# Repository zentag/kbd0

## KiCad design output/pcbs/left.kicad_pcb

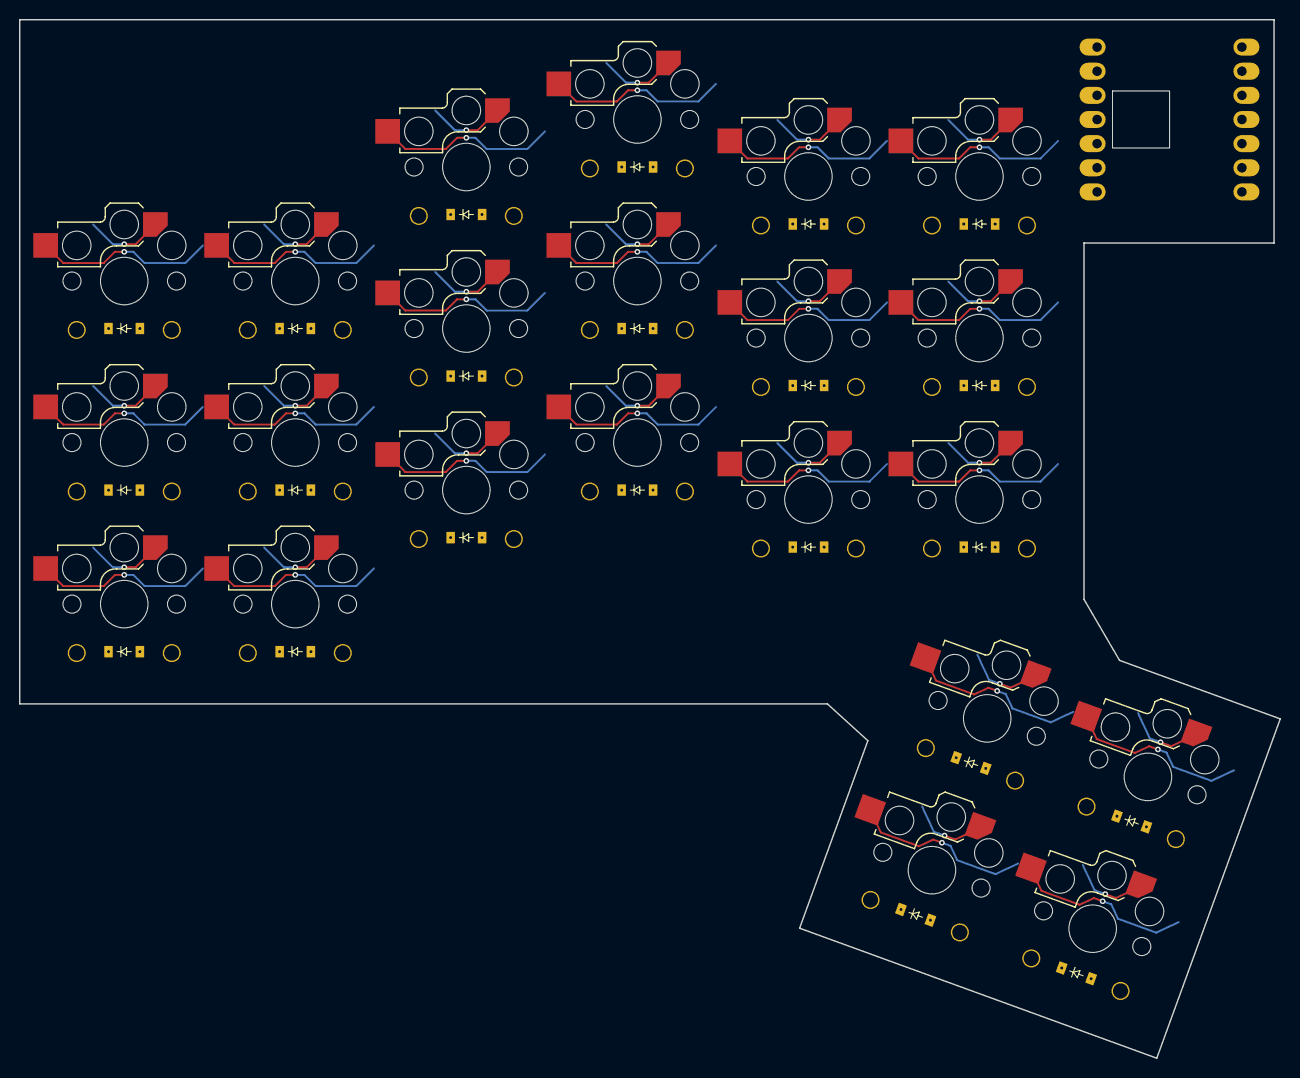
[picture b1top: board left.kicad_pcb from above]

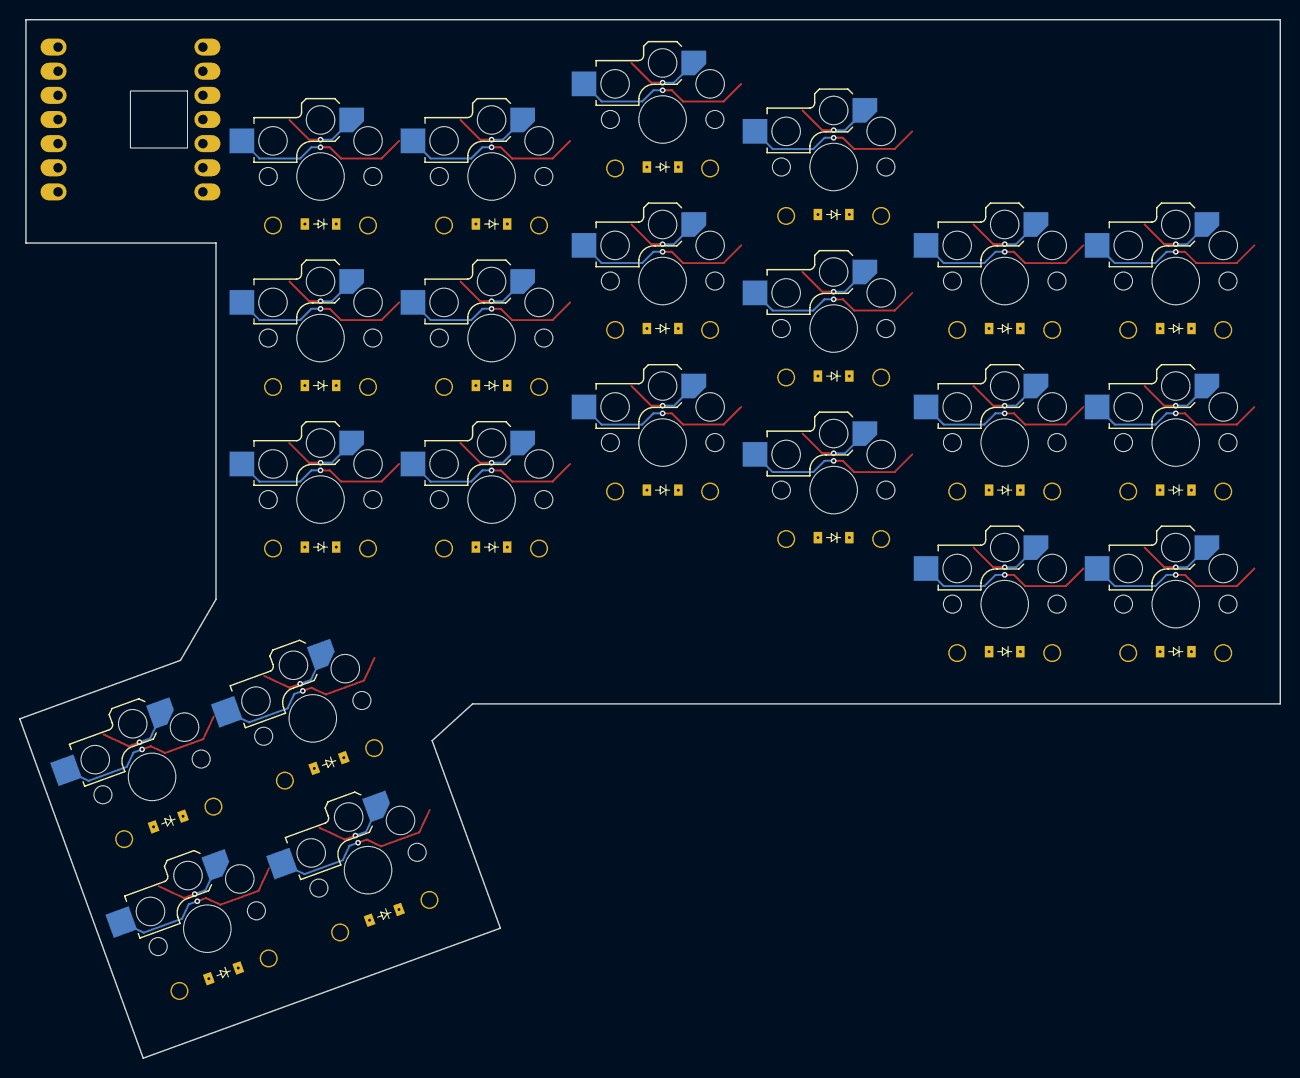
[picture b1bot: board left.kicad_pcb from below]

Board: 2 copper layers, 132.7 x 109.3 mm, 45 parts (22 on the bottom side), 33 nets.

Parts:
D1, D2, D3, D4, D5, D6, D7, D8, D9, D10, D11, D12, D13, D14, D15, D16, D17, D18, D19, D20, D21, D22: diode_tht_sod123
MCU1: xiao-ble; XIAO-BLE
S1, S2, S3, S4, S5, S6, S7, S8, S9, S10, S11, S12, S13, S14, S15, S16, S17, S18, S19, S20, S21, S22: switch_choc_v1_v2

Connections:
P0: MCU1.1, S1.1, S2.1, S3.1
P1: MCU1.2, S4.1, S5.1, S6.1
P2: MCU1.3, S7.1, S8.1, S9.1
P3: MCU1.4, S10.1, S11.1, S12.1
P4: MCU1.5, S13.1, S14.1, S15.1
P5: MCU1.6, S16.1, S17.1, S18.1
P6: D3.1, D6.1, D9.1, D12.1, D15.1, D18.1, MCU1.7
P7: D2.1, D5.1, D8.1, D11.1, D14.1, D17.1, D20.1, D22.1, MCU1.8
P8: D1.1, D4.1, D7.1, D10.1, D13.1, D16.1, D19.1, D21.1, MCU1.9
P9: MCU1.10, S19.1, S20.1
P10: MCU1.11, S21.1, S22.1
index_bottom: D13.2, S13.2
index_home: D14.2, S14.2
index_top: D15.2, S15.2
inner_bottom: D16.2, S16.2
inner_home: D17.2, S17.2
inner_top: D18.2, S18.2
left_bottom: D19.2, S19.2
left_top: D20.2, S20.2
middle_bottom: D10.2, S10.2
middle_home: D11.2, S11.2
middle_top: D12.2, S12.2
outer_bottom: D1.2, S1.2
outer_home: D2.2, S2.2
outer_top: D3.2, S3.2
pinky_bottom: D4.2, S4.2
pinky_home: D5.2, S5.2
pinky_top: D6.2, S6.2
right_bottom: D21.2, S21.2
right_top: D22.2, S22.2
ring_bottom: D7.2, S7.2
ring_home: D8.2, S8.2
ring_top: D9.2, S9.2

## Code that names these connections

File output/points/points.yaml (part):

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        autobind: 10
        skip: false
        asym: both
        colrow: pinky_bottom
        name: matrix_pinky_bottom
        zone:
            columns:
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        autobind: 10
        skip: false
        asym: both
        colrow: pinky_home
        name: matrix_pinky_home
        zone:
            columns:
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        autobind: 10
        skip: false
        asym: both
        colrow: pinky_top
        name: matrix_pinky_top
        zone:
            columns:
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
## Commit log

2025-06-14 add ergogen
2025-06-14 add config from website
2025-06-14 run ergogen
2025-06-14 draft layout
2025-06-21 change config outline
2025-06-21 add basic pcb ergogen cfg
2025-06-21 change outline to make space for MCU and battery
2025-06-21 run ergogen with new case
2025-06-22 finalize case
2025-06-22 add nrf footprint
2025-06-22 use kicad to export example switchplate
2026-06-25 redo the outlines lololol
2026-06-25 add kicad proj
2026-06-25 add switchplate
2026-06-25 minimize portrusion around uhhhhhhh the uhhhhhhh xio ble
2026-06-26 try autorouting with ergogen nets
2026-06-26 remove unnecessary internal MCU pads that caused errors
2026-06-26 can't believe that worked
2026-06-26 first passing pcb
2026-06-26 ignore dumb kicad .history dir
2026-06-26 reroute and do some other stuff I honestly forgot
2026-06-27 generate first gerber
2026-06-27 im tired of giving things names
2026-06-27 use cleoloide footprints
